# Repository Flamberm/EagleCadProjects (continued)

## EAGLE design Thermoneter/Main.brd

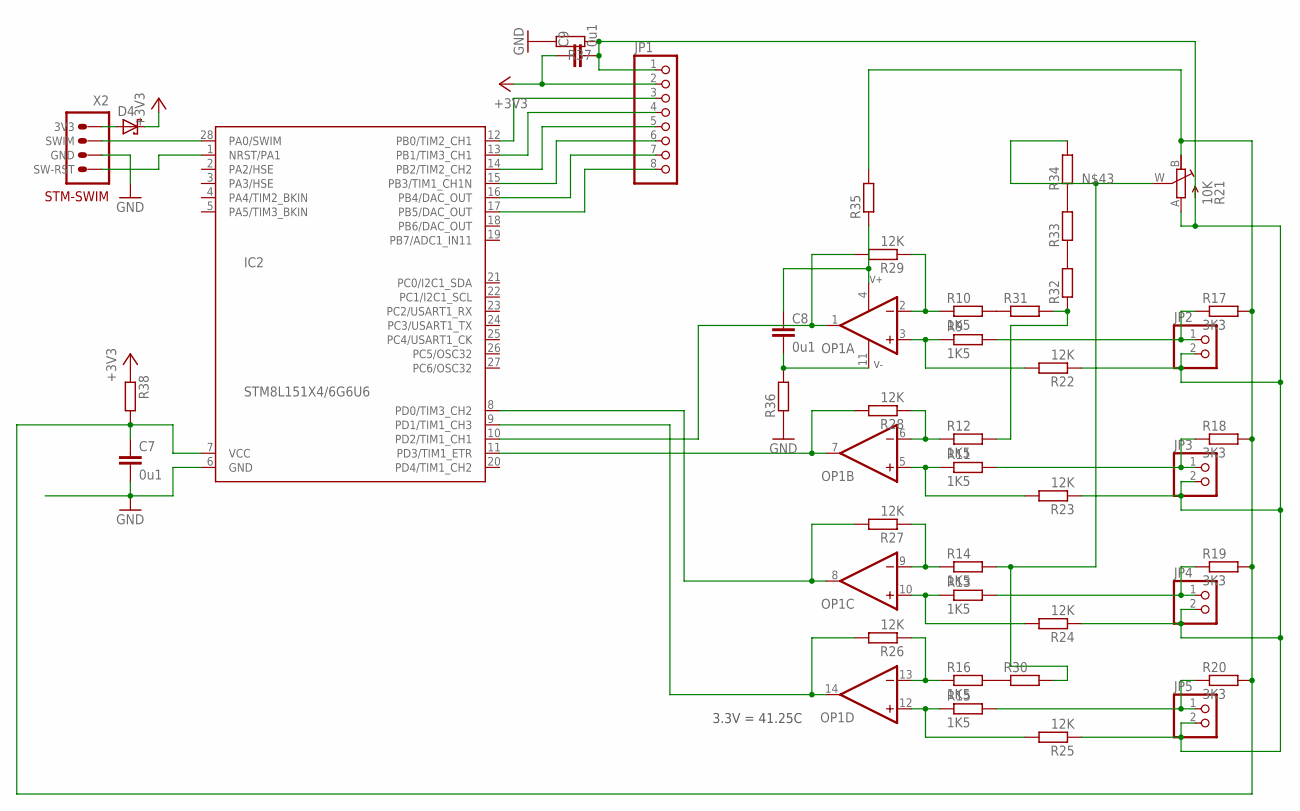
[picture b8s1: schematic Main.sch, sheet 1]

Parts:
C7, C8, C9: 0u1; C0805
D4: DIODE-SH_SOD523; SOD523
IC2: STM8L151X4/6G6U6; QFN28
JP1: PINHD-1X8; 1X08
JP2, JP3, JP4, JP5: PINHD-1X2; 1X02
OP1: OP-AMP-4LMV324IPT; TSSOP14
R9, R10, R11, R12, R13, R14, R15, R16: 1K5; R0805
R17, R18, R19, R20: 3K3; R0805
R21: 10K; RJ9W
R22, R23, R24, R25, R26, R27, R28, R29: 12K; R0805
R30, R31, R32, R33, R34, R35, R36, R37, R38: R_1206; R1206
X2: STM-SWIMPINS; 1X04/90

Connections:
273: R12.2, R31.2, R32.1
+3V3: C9.1, D4.C, JP1.2, R38.1; also elsewhere on the board
GND: C7.2, IC2.6 (GND), R36.1, R37.2, X2.3 (GND); also elsewhere on the board
unnamed: IC2.10 (PD2/TIM1_CH1), OP1.1 (OUT), R29.2
unnamed: IC2.11 (PD3/TIM1_ETR), OP1.7 (OUT), R28.2
unnamed: IC2.8 (PD0/TIM3_CH2), OP1.8 (OUT), R27.2
unnamed: IC2.9 (PD1/TIM1_CH3), OP1.14 (OUT), R26.2
unnamed: IC2.12 (PB0/TIM2_CH1), JP1.3
unnamed: IC2.13 (PB1/TIM3_CH1), JP1.4
unnamed: IC2.14 (PB2/TIM2_CH2), JP1.5
unnamed: IC2.15 (PB3/TIM1_CH1N), JP1.6
unnamed: IC2.16 (PB4/DAC_OUT), JP1.7
unnamed: IC2.17 (PB5/DAC_OUT), JP1.8
unnamed: IC2.28 (PA0/SWIM), X2.2 (SWIM)
unnamed: IC2.1 (NRST/PA1), X2.4 (SW-RST)
unnamed: D4.A, X2.1 (3V3)
unnamed: OP1.3 (+IN), R9.1, R22.2
unnamed: OP1.2 (-IN), R10.1, R29.1
unnamed: R10.2, R31.1
unnamed: OP1.6 (-IN), R12.1, R28.1
unnamed: OP1.10 (+IN), R13.1, R24.2
unnamed: OP1.9 (-IN), R14.1, R27.1
unnamed: OP1.12 (+IN), R15.1, R25.2
unnamed: OP1.13 (-IN), R16.1, R26.1
unnamed: JP5.1, R15.2, R20.1
unnamed: JP4.1, R13.2, R19.1
unnamed: JP3.1, R11.2, R18.1
unnamed: JP2.1, R9.2, R17.1
unnamed: OP1.5 (+IN), R11.1, R23.2
unnamed: R16.2, R30.1
unnamed: R14.2, R21.W (S), R30.2, R34.2
unnamed: R32.2, R33.1
unnamed: R33.2, R34.1
unnamed: C8.1, OP1.4 (V+), R35.1
unnamed: C8.2, OP1.11 (V-), R36.2
unnamed: C9.2, JP1.1, JP2.2, JP3.2, JP4.2, JP5.2, R21.A, R22.1, R23.1, R24.1, R25.1, R37.1
unnamed: C7.1, IC2.7 (VCC), R17.2, R18.2, R19.2, R20.2, R21.B (E), R35.2, R38.2

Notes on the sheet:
3.3V = 41.25C

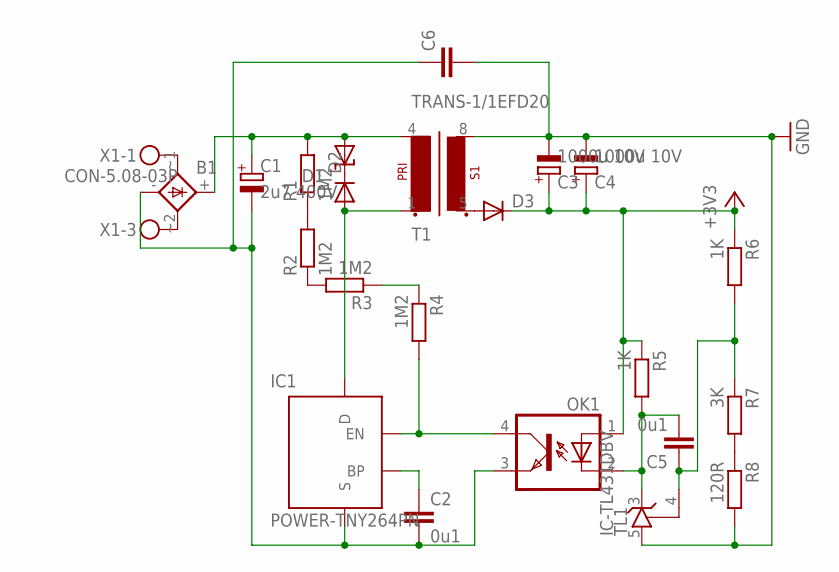
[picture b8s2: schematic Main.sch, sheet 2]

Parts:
B1: RECTIFIERSOIC-8; SOIC-4
C1: 2u7 400V; E5-10,5
C2, C5: 0u1; C0805
C3, C4: 1000u 10V; E5-10,5
C6: CAP_C50-024X044; C050-024X044
D1: SUPRESSORDO-204AC; DO15-12
D2, D3: DIODE_ES1J; DO214AC
IC1: POWER-TNY264PN; DIP-8B
OK1: OPTOTRANSPC817; DIL04
R1, R2, R3, R4: 1M2; R0805
R5, R6: 1K; R0805
R7: 3K; R0805
R8: 120R; R0805
T1: TRANS-1/1EFD20; EFD20_8PIN
TL1: IC-TL431DBV; SOT23-5L
X1: CON-5.08-03P; MKDSN1,5/3-5,08

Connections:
+3V3: C3.+, C4.+, D3.C, OK1.1 (A), R5.1, R6.1; also elsewhere on the board
GND: C3.-, C4.-, C6.2, R8.2, T1.8 (S1-2), TL1.5 (A); also elsewhere on the board
unnamed: B1.~1 (AC1), X1.1
unnamed: B1.~2 (AC2), X1.3
unnamed: B1.+, C1.+, D1.A, R1.2, T1.4 (P1-2)
unnamed: B1.-, C1.-, C2.2, C6.1, IC1.2 (S), IC1.3 (S), IC1.7 (S), IC1.8 (S), OK1.3 (EMIT)
unnamed: D1.C, D2.C
unnamed: D2.A, IC1.5 (D), T1.1 (P1-1)
unnamed: R1.1, R2.2
unnamed: R2.1, R3.2
unnamed: R3.1, R4.1
unnamed: IC1.4 (EN), OK1.4 (COL), R4.2
unnamed: C2.1, IC1.1 (BP)
unnamed: D3.A, T1.5 (S1-1)
unnamed: C5.2, OK1.2 (C), R5.2, TL1.3 (C)
unnamed: C5.1, R6.2, R7.1, TL1.4 (R)
unnamed: R7.2, R8.1

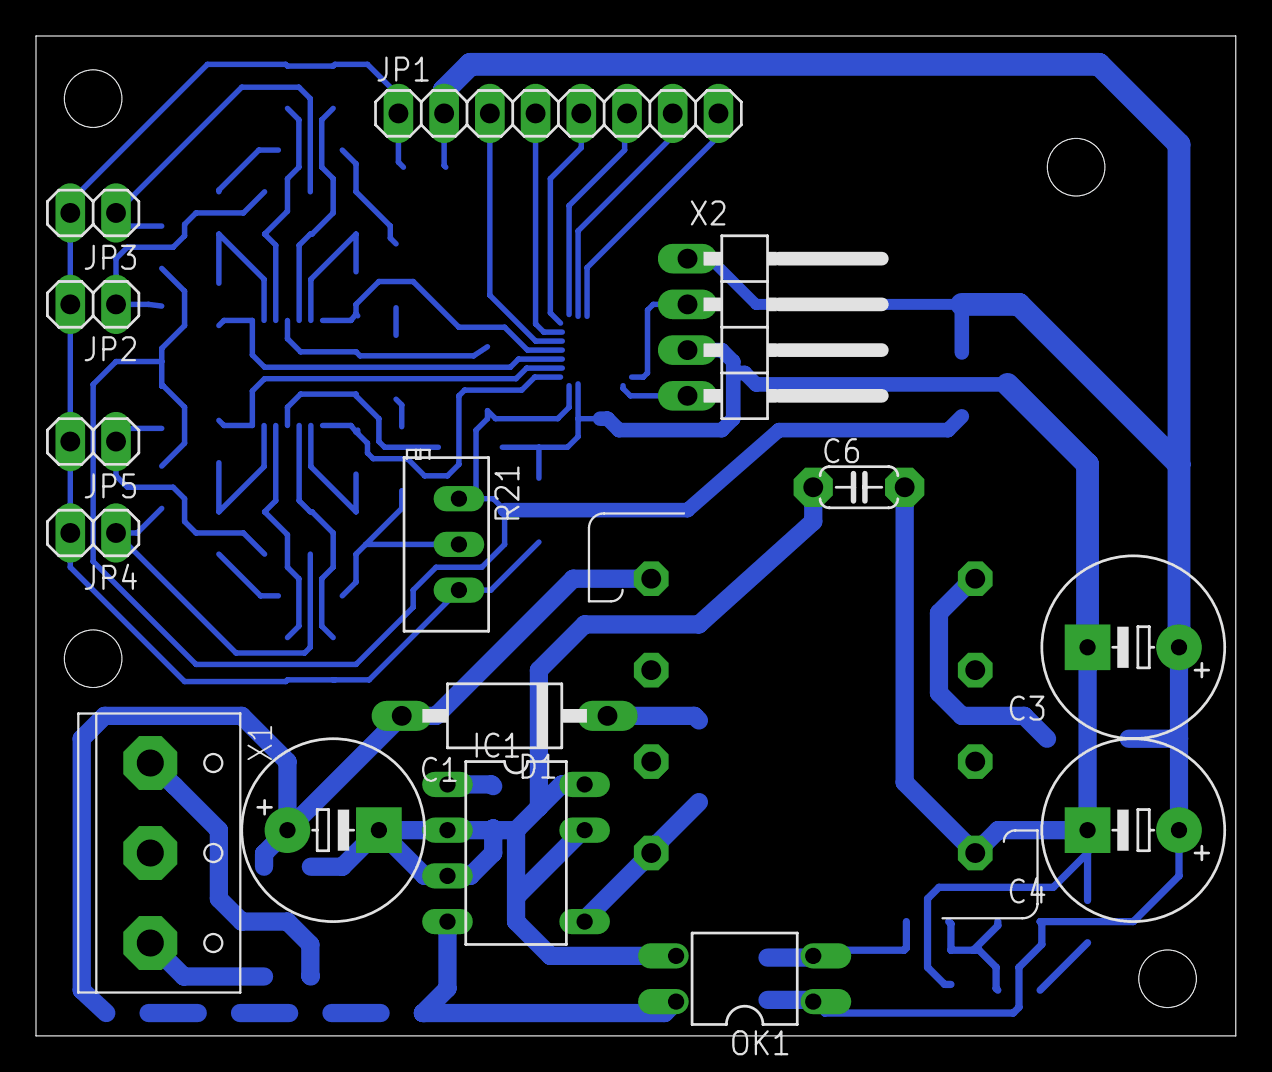
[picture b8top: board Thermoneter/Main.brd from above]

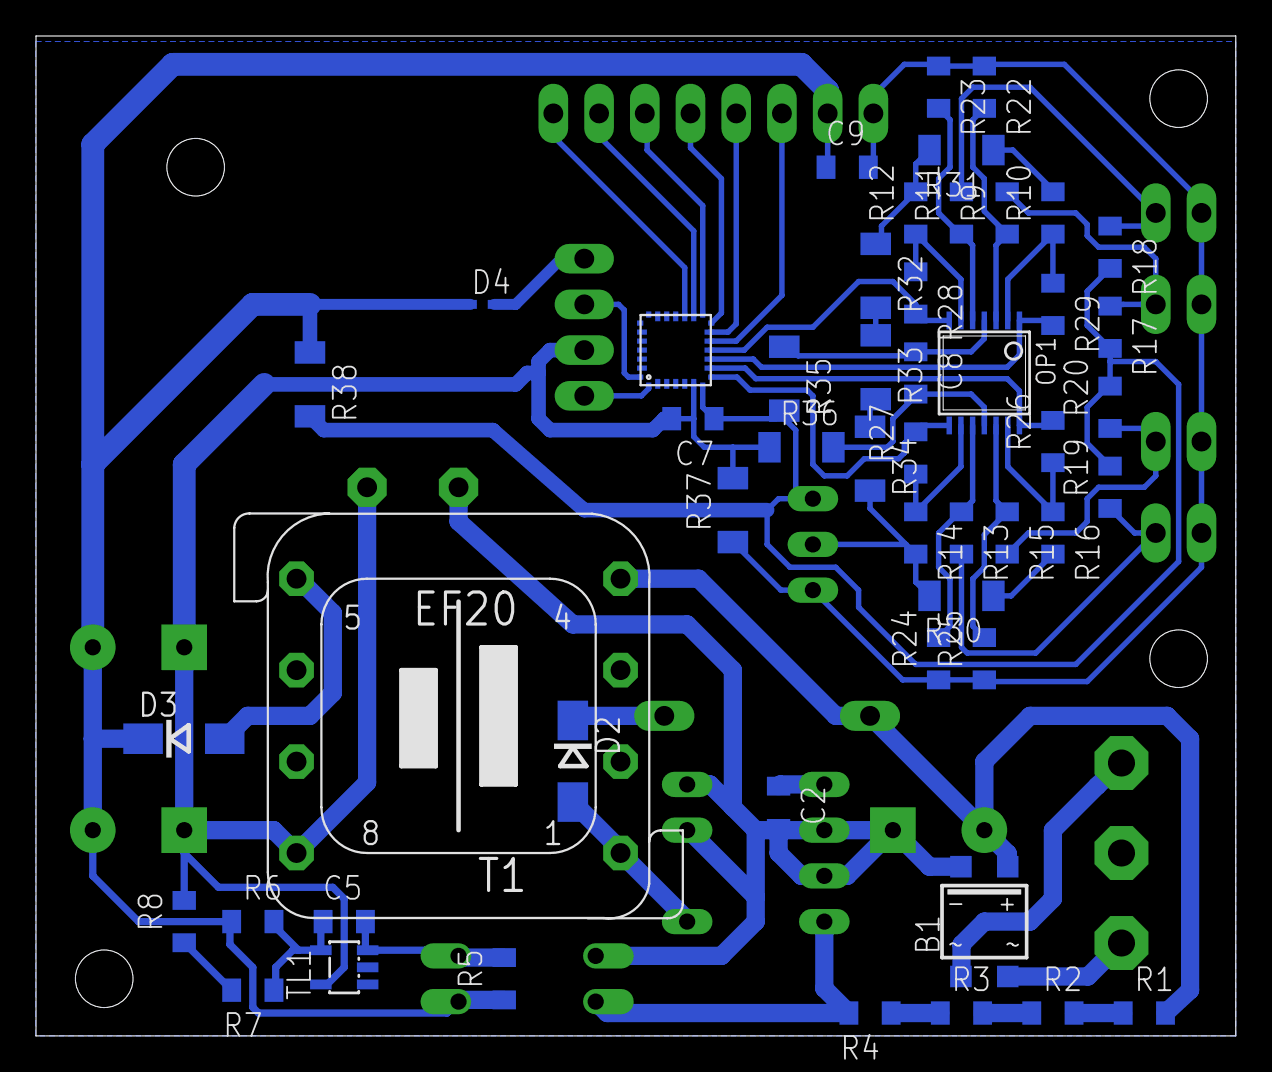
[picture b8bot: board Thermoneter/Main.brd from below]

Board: 2 copper layers, 66.7 x 55.5 mm, 65 parts (50 on the bottom side), 52 nets.
